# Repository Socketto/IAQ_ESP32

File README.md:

This board, designed with KiCad and programmed with Arduino, features an ESP-32 WROOM.  

The board can read CO2, TVOC, humidity, atmospheric pressure, and altitude values from multiple SPI sensors. The CO2 sensor used is the CCS811, and the board allows for the installation of two sensors, distinguished by different addresses.  

For programming, an external serial converter can be used, or it can be programmed directly via the USB port using the CH340G, which is mounted at the center of the board.

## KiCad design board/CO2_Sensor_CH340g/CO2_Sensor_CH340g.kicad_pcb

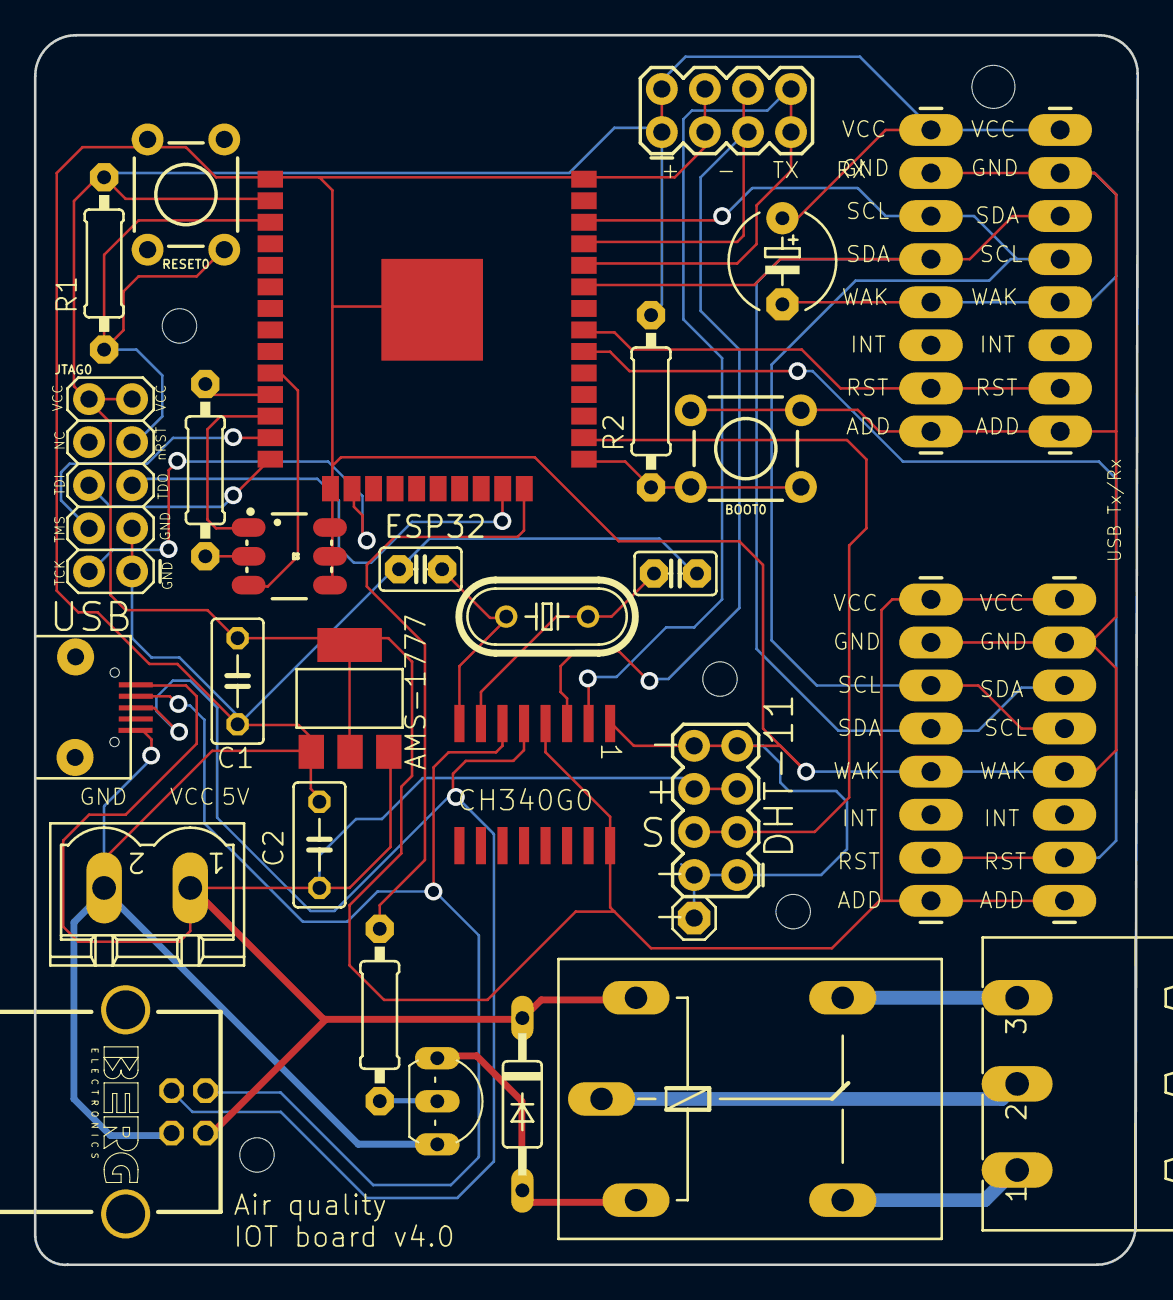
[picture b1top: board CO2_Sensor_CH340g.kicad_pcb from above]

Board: 2 copper layers, 65.0 x 72.5 mm, 36 parts (0 on the bottom side), 10 nets.

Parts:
AMS-1777: 3.3v; SOT223_111
BC547: BC547; TO92-_398
BOOT0: TACTILE_SWITCH_PTH_6.0MM_535
C1, C2: 100uF; C050-030X075_420
CH340G0: SOP16_338
D2: C2992_210
E$1, E$3, E$4, E$6: 1X08_LONGPADS_513
E$2, E$9: 2X4_513
E$5: MSTBV2_176
E$7: LED-TRICOLOR-5050_529
E$8: 1X01_420
E$10: MICR-USB
E$11: 12Mhz; HC49_S_204
E$12, E$13: 22pf; C025-025X050_420
E$15: G5LE_339
E$17: MSTBA3_176
E$18: 1000uf; E5-6_420
E$19: PN61729-S_130
ESP32: ESP-WROOM-32
JTAG0: 2X5_513
R1, R2: 10k; 0207_10_420
R3: 220; 0207_10_420
R4: 68Ω; 0207_10_420
RESET0: TACTILE_SWITCH_PTH_6.0MM_535
UNK_HOLE_0: dummyfp0
UNK_HOLE_1: dummyfp1
UNK_HOLE_2: dummyfp2
UNK_HOLE_3: dummyfp3
UNK_HOLE_4: dummyfp4

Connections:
S$13: E$3.5, E$6.6
S$15: E$1.6, E$4.5
S$16: E$1.4, E$4.4
S$23: JTAG0.7, R1.1
S$26: E$2.1, E$2.2
S$29: E$8.1, E$9.2, E$9.7
S$43: E$2.4, E$3.4, E$3.7, E$4.7
S$64: E$3.1, E$3.8
S$94: JTAG0.9, JTAG0.10
S$95: C1.1, JTAG0.1, JTAG0.3

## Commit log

2025-03-07 [ADD] First commit
2025-04-18 [UPD] Update gitignore
2025-04-18 [UPD] Update board
